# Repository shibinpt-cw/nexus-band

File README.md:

# Nexus Band

A watch that controls the AI assistant on my laptop. I hold the side button and say what I want ("open Notepad, type this and send it to..."), and the assistant on the laptop does it. If an action is risky, the watch asks me first with Approve and Reject buttons.

I'm building it for Hack Club Fallen.

## Why I'm building this

I spend hours at my desk waiting for builds, tests and scripts. When I get up, the laptop sits there until I come back to press Enter or approve something. A normal smartwatch only shows notifications, so it can't help with that.

Nexus Band is a remote for my own assistant, ATS 10, a Python program that runs on the laptop. The watch and the laptop talk over my Wi-Fi. I can walk around the room, tell the laptop what to do, see what it is doing, and approve or reject its actions from my wrist.

## How the watch and the laptop work together

```
  watch (ESP32-S3)                                laptop (ATS 10)
  ---------------                                 ---------------
  hold button + speak  -- 16 kHz audio (WSS) -->  speech -> assistant -> opens apps,
  tap a quick command  -- JSON command (WSS) -->  types, sends messages, runs commands
  Approve / Reject     -- JSON confirm (WSS) -->  continues or cancels the action
  screen + buzz        <-- activity log, confirmation requests --
```

The watch uses the same API as the assistant's phone dashboard:

| Step | Endpoint | What it carries |
|---|---|---|
| Pair | `POST https://<laptop>:8001/login` | one-time key shown on the laptop, returns a token |
| Commands and status | `wss://<laptop>:8001/ws?token=...` | `{"type":"command","text":"..."}`, `{"type":"confirm","decision":"confirm"}`, and the laptop's log and `confirmation_request` messages |
| Voice | `wss://<laptop>:8001/ws/phone-audio?token=...` | raw 16 kHz 16-bit mono audio from the two microphones |

## Hardware

Everything is on one 4-layer PCB, 71 x 40 mm, that sits behind the display. All the parts are on the back, facing the battery, so the front lies flat against the display.

| Block | Part | Notes |
|---|---|---|
| MCU | ESP32-S3-WROOM-1-N16R8 | Wi-Fi, native USB, 16 MB flash, 8 MB PSRAM |
| Display | Newhaven NHD-2.4-240320AF-CSXP-CTP | 2.4" IPS, 240 x 320, ST7789 over SPI, FT5426 capacitive touch |
| Microphones | 2 x ICS-43434 | I2S, 30 mm apart on the right edge |
| Speaker | MAX98357A + 1511 speaker | I2S class-D amplifier |
| Haptics | DRV2605L + LRA motor | wrist buzz when the laptop needs an answer |
| Power | 1000 mAh Li-Po, TP4056 charger, AP2112K 3.3 V | charges at 400 mA from the dock |
| Dock | 4-pin magnetic pogo connector | 5 V charging and USB for flashing |
| Controls | side button (also BOOT), power slide switch | |

### Power and battery life

The slide switch on the bottom edge turns the 3.3 V regulator on and off. With it off, the charger, the battery divider, the amplifier and the haptic driver are still connected, but together they draw about 15 µA, so a charged cell keeps for months. The dock charges the battery with the switch in either position.

I plan to leave the watch switched on and connected all day. The screen turns off after 15 s without use. The side button or a tap wakes it, and so does any message or approval request from the laptop, which also makes the watch buzz.

I haven't measured the runtime yet. My estimate for the 1000 mAh cell is about 10 h with the screen on the whole time and about a day of normal use with the screen sleeping, so it will charge on the dock overnight. If the battery falls below 3.35 V off the dock, the firmware puts the ESP32 into deep sleep to protect the cell.

### Size

The watch body is 85 x 48 mm, or 99 mm across the strap lugs, and 17.5 mm thick. The thickness adds up as bezel 1.0 + display 4.1 + foam 0.5 + PCB 1.6 + parts 3.5 + battery 5.2 + floor 1.4.

### Schematic

PDF: [docs/images/schematic.pdf](docs/images/schematic.pdf)

### PCB

| Back (parts) | Front (display side) |
|---|---|
|  |  |

| 3D, back | 3D, front |
|---|---|
|  |  |

Layer stack: front signal / ground plane / 3.3 V plane / back signal and parts. The strip under the ESP32 antenna has no copper on any layer.

The slot and the notch on the right are for the display's two flex tails. They fold around the board edge and plug into the connectors on the back. That fold reverses the 40-pin connector's numbering: connector pad n is display pin 41 - n. The schematic shows both numbers.

The files in this repo pass KiCad's checks: the [ERC report](docs/erc_report.txt) has 0 violations, and the [DRC report](docs/drc_report.txt) has 0 violations and 0 unconnected pads.

### Pin map

| Function | ESP32-S3 pin |
|---|---|
| Display CS / MOSI / SCK / DC / RST / TE | IO10 / IO11 / IO12 / IO13 / IO14 / IO21 |
| Backlight PWM | IO9 |
| I2C SDA / SCL (touch 0x38, haptics 0x5A) | IO17 / IO18 |
| Touch INT / RST | IO16 / IO15 |
| Microphones SCK / WS / SD | IO5 / IO6 / IO7 |
| Amplifier BCLK / LRCLK / DIN / shutdown | IO40 / IO41 / IO42 / IO39 |
| Battery voltage (1/2 divider) | IO4 |
| Dock detect | IO8 |
| Side button / BOOT | IO0 |
| USB D- / D+ | IO19 / IO20 |

## Case

The case is three parts printed in PETG, and it takes a standard 22 mm quick-release strap.

| Assembled | Exploded |
|---|---|
|  |  |

| Back (strap lugs, screws, speaker grille) | Top edge (charging connector, speaker slots) |
|---|---|
|  |  |

| Part | File | What it does |
|---|---|---|
| Front frame | [`cad/front_frame.step`](cad/front_frame.step) | Bezel with the display window, display pocket, PCB pocket, the two microphone holes (with seats for foam gaskets) and the screw pilots |
| Back shell | [`cad/back_shell.step`](cad/back_shell.step) | Battery, speaker and motor bay with locating ribs, a ledge that clamps the PCB edge, button and power-switch openings on the bottom edge, the charging connector pocket and four speaker slots on the top edge, the speaker grille and four 22 mm strap lugs |
| Button cap | [`cad/button_cap.step`](cad/button_cap.step) | Plunger for the side button; its flange sits inside the back shell |

### Printed parts

| Front frame, outside | Front frame, inside |
|---|---|
|  |  |

| Back shell, inside | Back shell, outside |
|---|---|
|  |  |

| Back shell, top edge | Button cap |
|---|---|
|  |  |

| Part | Size | PETG |
|---|---|---|
| Front frame | 85 x 48 x 7.4 mm | about 13 g |
| Back shell | 99 x 48 x 10.1 mm (with lugs) | about 20 g |
| Button cap | 4.6 x 4.8 x 1.5 mm | under 1 g |

The CAD source is [`cad/nexus_band_case.FCStd`](cad/nexus_band_case.FCStd), made in FreeCAD 1.1. It also holds the PCB, display, battery, speaker and motor as reference parts. The whole assembly is in one file, [`cad/nexus_band_assembly.step`](cad/nexus_band_assembly.step).

### How it fits together

The PCB has no mounting holes, so the case clamps it. The board drops into a 1.6 mm pocket in the front frame, and a 0.8 mm ledge on the back shell presses on its edge. The ledge is cut away where the ESP32 module, the touch connector, the switches and the microphones reach the edge.

The display sits face down in the front frame on 0.5 mm foam tape. The window matches its viewing area, 49.96 x 37.72 mm, which sits 2.5 mm off centre, away from the flex tails.

Four M2 x 12 self-tapping screws go through the ends of the back shell into the front frame. They pass outside the board.

The battery is in the middle and the speaker and motor are on the left. Nothing sits over the antenna strip. The speaker stands on 1 mm pads, which leaves an air gap under it. Sound leaves through the floor grille, a shallow channel to the edge, and four slots in the top edge, so it can still be heard when the floor is against the wrist.

The magnetic dock connector is glued into the pocket on the top edge, next to the dock pads on the PCB. The cable snaps on from the side, and the same connector carries USB for flashing.

Any 22 mm quick-release strap fits. Its spring bars click into the 1.1 mm holes in the lugs without tools.

The power switch lever sits in a slot on the bottom edge. It slides with a fingernail or a toothpick.

### Printing

Print the front frame face down and the back shell floor down, with 0.2 mm layers and no supports.

## Firmware

The firmware is a PlatformIO project in [`firmware/`](firmware). It starts the display, touch, microphones, speaker and haptics, then pairs with the laptop. While I hold the button it streams my voice, and it shows the assistant's messages and confirmation prompts on the screen.

To flash it:

1. Copy the settings block from `firmware/include/config.h` into a new `firmware/include/config_local.h` and fill in the Wi-Fi name, password, laptop address and the one-time key the laptop shows.
2. Put the watch on the dock, hold the side button while connecting it the first time, then `pio run -t upload`.

The firmware compiles with `pio run` and takes about 1 MB of the 16 MB flash. It has not run on hardware yet, because the board is not built.

## Building one

Nobody has built this watch yet, including me, so treat these steps as the plan. I will correct them after my own build.

### 1. Order the board

Upload three files from [`pcb/`](pcb) to JLCPCB: `gerbers.zip` for the board, `jlcpcb_bom.csv` for the parts and `jlcpcb_cpl.csv` for the part positions. Choose 4 layers, 1.6 mm, HASL, and assembly on the bottom side. Check the part rotations in JLCPCB's preview before paying, because their rotation convention sometimes differs from KiCad's.

The factory fits every part on the board except the 6-pin touch connector, J2. That one comes from DigiKey and has a 1.0 mm pitch, so a normal soldering iron can do it.

### 2. Order the rest

[`bom.csv`](bom.csv) lists everything else with a link: the display, touch connector, speaker, vibration motor and magnetic connector from DigiKey, the battery, a 22 mm strap, four M2 x 12 screws and 0.5 mm foam tape. The battery must have its own protection board, because the PCB does not have one.

### 3. Print the case

Print `front_frame.step`, `back_shell.step` and `button_cap.step` from [`cad/`](cad) in PETG with 0.2 mm layers and no supports. The front frame prints face down and the back shell prints floor down. Measure the magnetic connector first. The pocket for it is 13.5 x 5 mm, and if your connector is a different size you can change the pocket in `nexus_band_case.FCStd`.

### 4. Solder the wires

Solder the touch connector J2 to the board. Then solder wires to the labelled pads on the back: the battery to B+ and B-, the speaker to S+ and S-, the motor to M+ and M-, and the magnetic connector to the four dock pads marked 5V, D-, D+ and GND. Fit the other half of the magnetic connector to a cut USB cable with the same four wires. Leave the power switch off while you solder the battery.

### 5. Test before closing the case

Plug in the dock cable. The red LED means charging and the green LED means full. Switch the watch on and flash the firmware (see [Firmware](#firmware)). Check the screen, touch, both microphones, the speaker and the buzz before the board goes into the case.

### 6. Assemble

1. Stick 0.5 mm foam tape on the front of the PCB, with small rings around the two microphone holes.
2. Lay the display face down in the front frame. Fold its two flex tails through the slot and the notch in the PCB, and lock them into J1 and J2 on the back.
3. Lower the PCB into its pocket in the front frame.
4. Put the speaker on its four pads in the back shell with the sound side down, press the motor into its ring, glue the magnetic connector into its pocket, and lay the battery in the middle.
5. Drop the button cap into its slot on the bottom edge.
6. Close the back shell over the front frame and fit the four screws.
7. Click the strap's spring bars into the lugs.

## Repository

```
nexus-band/
├── README.md
├── bom.csv                  parts list with links
├── pcb/                     KiCad 10 project
│   ├── nexus_band.kicad_pro / .kicad_sch / .kicad_pcb / .kicad_prl
│   ├── nexus_band.pretty/   footprints for the wire pads
│   ├── gerbers.zip          fabrication files (gerbers + drill)
│   ├── jlcpcb_bom.csv       parts list in JLCPCB's format, with LCSC numbers
│   ├── jlcpcb_cpl.csv       part positions in JLCPCB's format
│   └── nexus_band-pos.csv   pick-and-place positions as KiCad exports them
├── cad/                     case parts (STEP), FreeCAD source, PCB and assembly models
├── firmware/                ESP32-S3 firmware (PlatformIO)
└── docs/                    schematic PDF, renders, ERC / DRC reports
```

## Bill of materials

The first working watch costs about $252. That pays for a 5-board PCB order with two boards assembled, which is the factory minimum. It also covers the display, battery, speaker, motor, dock connector, strap and case screws, a 1 kg spool of PETG for the case, a soldering iron, shipping and import duty. The JLCPCB fees, shipping and duty lines are estimates until I have real quotes, and so are the strap, screws and foam tape, which are generic parts that any shop sells. The full list with links is in [`bom.csv`](bom.csv).

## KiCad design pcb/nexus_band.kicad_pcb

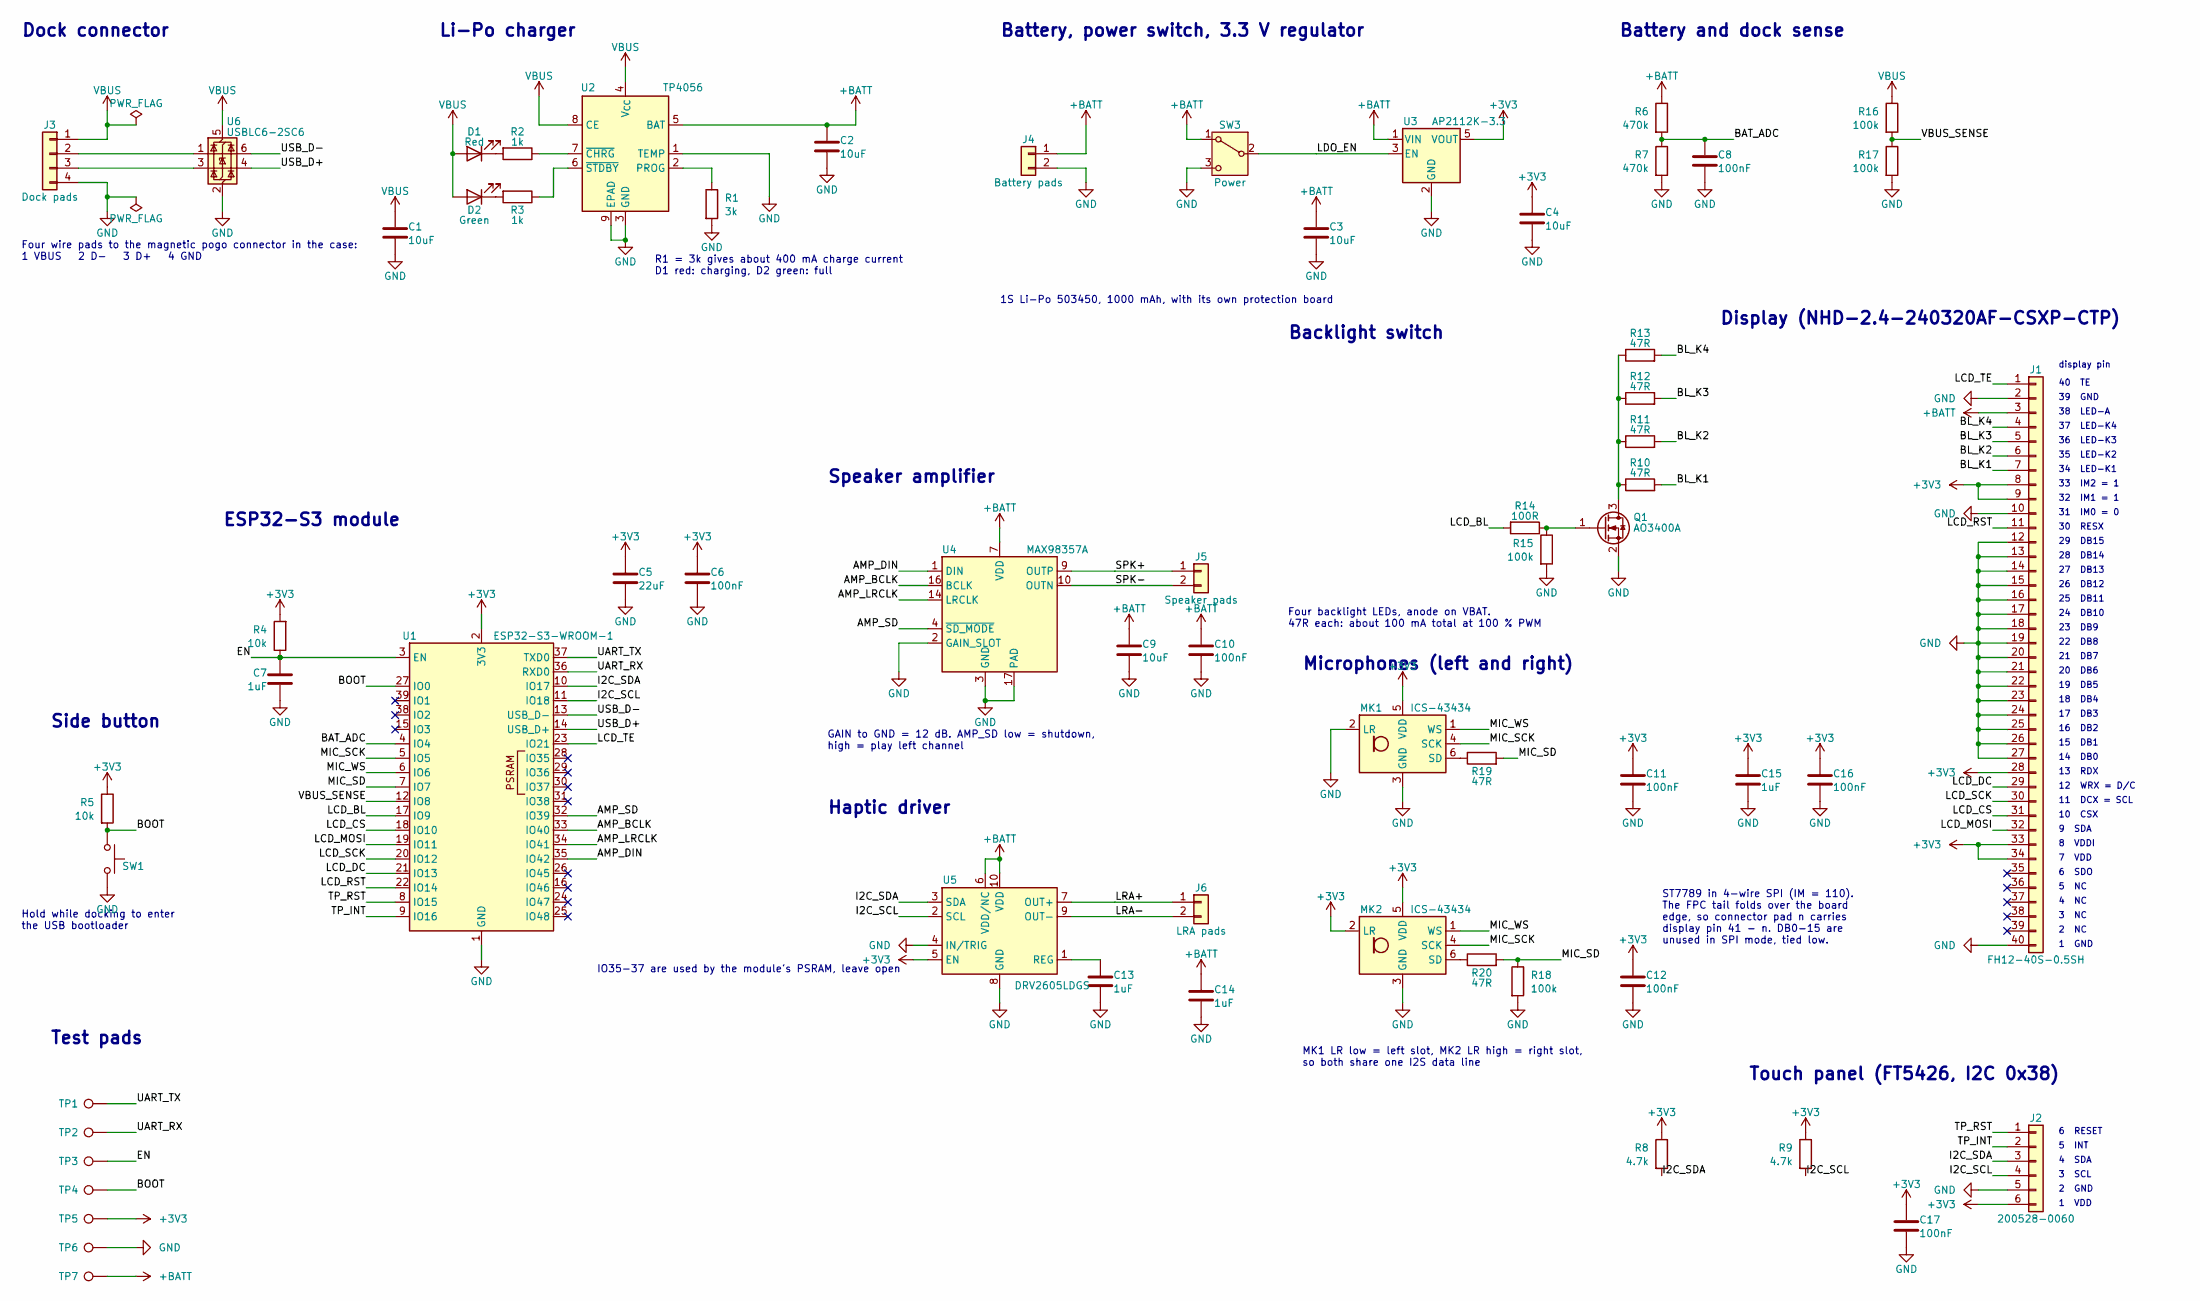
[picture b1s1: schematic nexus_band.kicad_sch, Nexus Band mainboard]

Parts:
C1, C2, C3, C4, C9: 10uF; C_0603_1608Metric
C5: 22uF; C_0805_2012Metric
C6, C8, C10, C11, C12, C16, C17: 100nF; C_0603_1608Metric
C7, C13, C14, C15: 1uF; C_0603_1608Metric
D1: Red; LED_0603_1608Metric
D2: Green; LED_0603_1608Metric
J1: FH12-40S-0.5SH; Hirose_FH12-40S-0.5SH_1x40-1MP_P0.50mm_Horizontal; MPN FH12-40S-0.5SH(55)
J2: 200528-0060; Molex_200528-0060_1x06-1MP_P1.00mm_Horizontal; MPN 2005280060
J3: Dock pads; WirePads_1x04_P2.54mm
J4: Battery pads; WirePads_1x02_P2.54mm
J5: Speaker pads; WirePads_1x02_P2.54mm
J6: LRA pads; WirePads_1x02_P2.54mm
MK1, MK2: ICS-43434; InvenSense_ICS-43434-6_3.5x2.65mm; MPN ICS-43434
Q1: AO3400A; SOT-23; MPN AO3400A
R1: 3k; R_0603_1608Metric
R2, R3: 1k; R_0603_1608Metric
R4, R5: 10k; R_0603_1608Metric
R6, R7: 470k; R_0603_1608Metric
R8, R9: 4.7k; R_0603_1608Metric
R10, R11, R12, R13, R19, R20: 47R; R_0603_1608Metric
R14: 100R; R_0603_1608Metric
R15, R16, R17, R18: 100k; R_0603_1608Metric
SW1: B3U-3000P; SW_SPST_B3U-3000P; MPN B3U-3000P
SW3: Power; SW_SPDT_PCM12; MPN PCM12SMTR
TP1: UART_TX; TestPoint_Pad_D1.5mm
TP2: UART_RX; TestPoint_Pad_D1.5mm
TP3: EN; TestPoint_Pad_D1.5mm
TP4: BOOT; TestPoint_Pad_D1.5mm
TP5: +3V3; TestPoint_Pad_D1.5mm
TP6: GND; TestPoint_Pad_D1.5mm
TP7: +BATT; TestPoint_Pad_D1.5mm
U1: ESP32-S3-WROOM-1; MPN ESP32-S3-WROOM-1-N16R8
U2: TP4056; SOIC-8-1EP_3.9x4.9mm_P1.27mm_EP2.41x3.3mm; MPN TP4056
U3: AP2112K-3.3; SOT-23-5; MPN AP2112K-3.3TRG1
U4: MAX98357A; TQFN-16-1EP_3x3mm_P0.5mm_EP1.23x1.23mm; MPN MAX98357AETE+T
U5: DRV2605LDGS; TSSOP-10_3x3mm_P0.5mm; MPN DRV2605LDGSR
U6: USBLC6-2SC6; SOT-23-6; MPN USBLC6-2SC6

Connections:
+3V3: C4.1, C5.1, C6.1, C11.1, C12.1, C15.1, C16.1, C17.1, J1.8, J1.9, J1.28, J1.33, J1.34, J2.6, MK1.5 (VDD), MK2.2 (LR), MK2.5 (VDD), R4.2, R5.1, R8.1, R9.1, TP5.1, U1.2 (3V3), U3.5 (VOUT), U5.5 (EN)
+BATT: C2.1, C3.1, C9.1, C10.1, C14.1, J1.3, J4.1, R6.1, SW3.1 (A), TP7.1, U2.5 (BAT), U3.1 (VIN), U4.7 (VDD), U4.8 (VDD), U5.6 (VDD/NC), U5.10 (VDD)
/AMP_BCLK: U1.33 (IO40), U4.16 (BCLK)
/AMP_DIN: U1.35 (IO42), U4.1 (DIN)
/AMP_LRCLK: U1.34 (IO41), U4.14 (LRCLK)
/AMP_SD: U1.32 (IO39), U4.4 (~SD_MODE)
/BAT_ADC: C8.1, R6.2, R7.1, U1.4 (IO4)
/BL_K1: J1.7, R10.2
/BL_K2: J1.6, R11.2
/BL_K3: J1.5, R12.2
/BL_K4: J1.4, R13.2
/BOOT: R5.2, SW1.1, TP4.1, U1.27 (IO0)
/EN: C7.1, R4.1, TP3.1, U1.3 (EN)
/I2C_SCL: J2.4, R9.2, U1.11 (IO18), U5.2 (SCL)
/I2C_SDA: J2.3, R8.2, U1.10 (IO17), U5.3 (SDA)
/LCD_BL: R14.2, U1.17 (IO9)
/LCD_CS: J1.31, U1.18 (IO10)
/LCD_DC: J1.29, U1.21 (IO13)
/LCD_MOSI: J1.32, U1.19 (IO11)
/LCD_RST: J1.11, U1.22 (IO14)
/LCD_SCK: J1.30, U1.20 (IO12)
/LCD_TE: J1.1, U1.23 (IO21)
/LDO_EN: SW3.2 (B), U3.3 (EN)
/LRA+: J6.1, U5.7 (OUT+)
/LRA-: J6.2, U5.9 (OUT-)
/MIC_SCK: MK1.4 (SCK), MK2.4 (SCK), U1.5 (IO5)
/MIC_SD: R18.1, R19.2, R20.2, U1.7 (IO7)
/MIC_WS: MK1.1 (WS), MK2.1 (WS), U1.6 (IO6)
/SPK+: J5.1, U4.9 (OUTP)
/SPK-: J5.2, U4.10 (OUTN)
/TP_INT: J2.2, U1.9 (IO16)
/TP_RST: J2.1, U1.8 (IO15)
/UART_RX: TP2.1, U1.36 (RXD0)
/UART_TX: TP1.1, U1.37 (TXD0)
/USB_D+: U1.14 (USB_D+), U6.4 (I/O2)
/USB_D-: U1.13 (USB_D-), U6.6 (I/O1)
/VBUS_SENSE: R16.2, R17.1, U1.12 (IO8)
GND: C1.2, C2.2, C3.2, C4.2, C5.2, C6.2, C7.2, C8.2, C9.2, C10.2, C11.2, C12.2, C13.2, C14.2, C15.2, C16.2, C17.2, J1.2, J1.10, J1.12, J1.13, J1.14, J1.15, J1.16, J1.17, J1.18, J1.19, J1.20, J1.21, J1.22, J1.23, J1.24, J1.25, J1.26, J1.27, J1.40, J2.5, J3.4, J4.2, MK1.2 (LR), MK1.3 (GND), MK2.3 (GND), Q1.2 (S), R1.2, R7.2, R15.2, R17.2, R18.2, SW1.2, SW3.3 (C), TP6.1, U1.1 (GND), U1.40 (GND), U1.41 (GND), U2.1 (TEMP), U2.3 (GND), U2.9 (EPAD), U3.2 (GND), U4.2 (GAIN_SLOT), U4.3 (GND), U4.11 (GND), U4.15 (GND), U4.17 (PAD), U5.4 (IN/TRIG), U5.8 (GND), U6.2 (GND)
unnamed: D1.1 (K), R2.2
unnamed: D2.1 (K), R3.2
unnamed: J3.2, U6.1 (I/O1)
unnamed: J3.3, U6.3 (I/O2)
unnamed: MK1.6 (SD), R19.1
unnamed: MK2.6 (SD), R20.1
unnamed: Q1.3 (D), R10.1, R11.1, R12.1, R13.1
unnamed: Q1.1 (G), R14.1, R15.1
unnamed: R1.1, U2.2 (PROG)
unnamed: R2.1, U2.7 (~CHRG)
unnamed: R3.1, U2.6 (~STDBY)
unnamed: C13.1, U5.1 (REG)
VBUS: C1.1, D1.2 (A), D2.2 (A), J3.1, R16.1, U2.4 (V_{CC}), U2.8 (CE), U6.5 (VBUS)

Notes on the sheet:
Dock connector
Four wire pads to the magnetic pogo connector in the case: 1 VBUS 2 D- 3 D+ 4 GND
Li-Po charger
R1 = 3k gives about 400 mA charge current D1 red: charging, D2 green: full
Battery, power switch, 3.3 V regulator
1S Li-Po 503450, 1000 mAh, with its own protection board
Battery and dock sense
ESP32-S3 module
IO35-37 are used by the module's PSRAM, leave open
Side button
Hold while docking to enter the USB bootloader
Test pads
Speaker amplifier
GAIN to GND = 12 dB. AMP_SD low = shutdown, high = play left channel
Haptic driver
Microphones (left and right)
MK1 LR low = left slot, MK2 LR high = right slot, so both share one I2S data line
Backlight switch
Four backlight LEDs, anode on VBAT. 47R each: about 100 mA total at 100 % PWM
Display (NHD-2.4-240320AF-CSXP-CTP)
40 TE
39 GND
38 LED-A
37 LED-K4
36 LED-K3
35 LED-K2
34 LED-K1
33 IM2 = 1
32 IM1 = 1
31 IM0 = 0
30 RESX
29 DB15
28 DB14
27 DB13
26 DB12
25 DB11
24 DB10
23 DB9
22 DB8
21 DB7

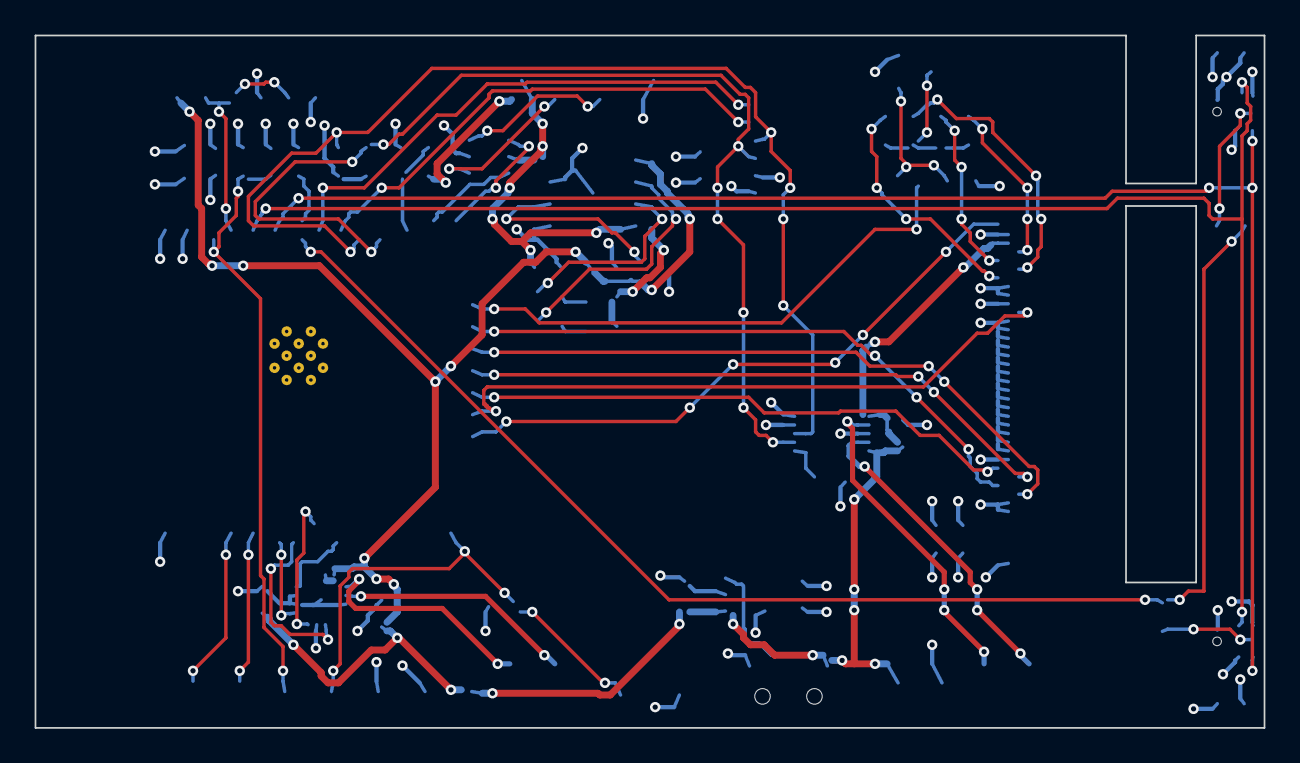
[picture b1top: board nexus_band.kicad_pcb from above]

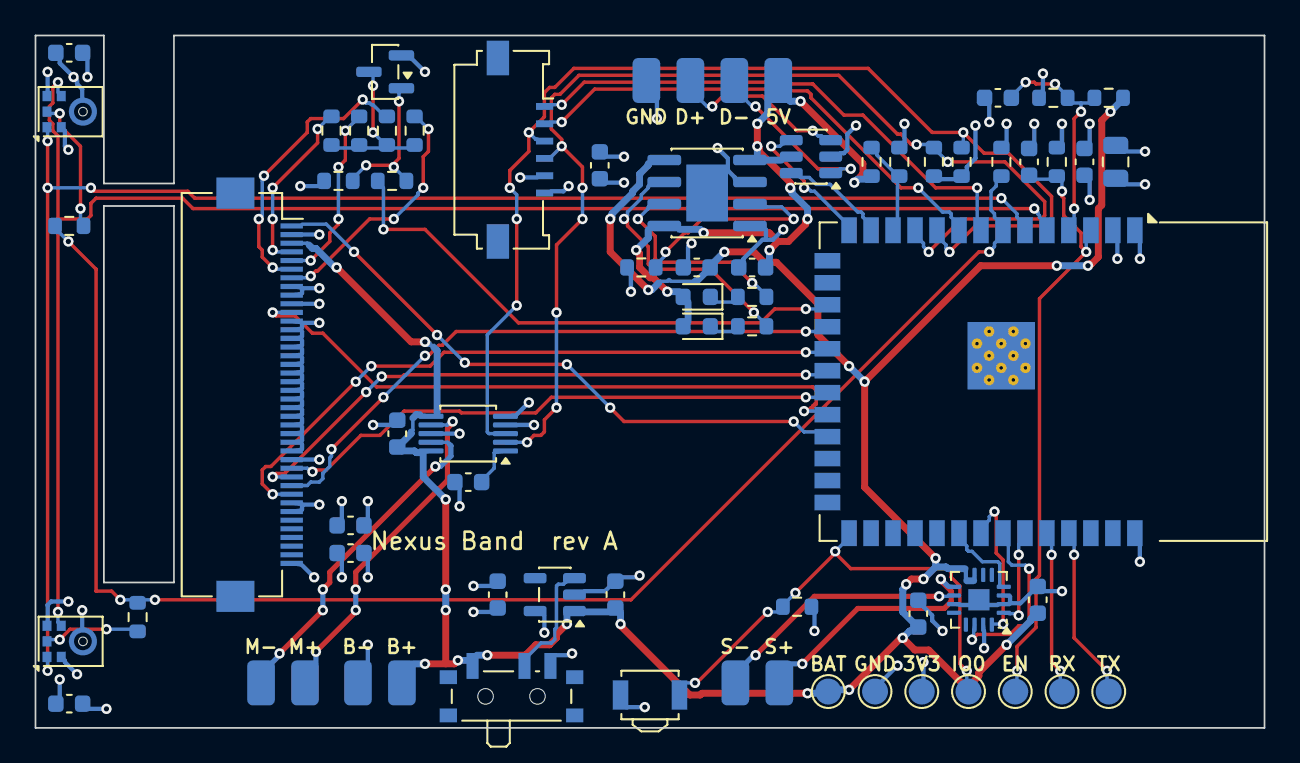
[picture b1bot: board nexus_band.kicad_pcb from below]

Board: 4 copper layers, 71.0 x 40.0 mm, 63 parts (63 on the bottom side), 51 nets.

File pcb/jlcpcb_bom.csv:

Comment,Designator,Footprint,LCSC Part #
10uF,"C1,C2,C3,C4,C9",C_0603_1608Metric,C19702
22uF,C5,C_0805_2012Metric,C45783
100nF,"C6,C8,C10,C11,C12,C16,C17",C_0603_1608Metric,C14663
1uF,"C7,C13,C14,C15",C_0603_1608Metric,C15849
Red,D1,LED_0603_1608Metric,C2286
Green,D2,LED_0603_1608Metric,C12624
FH12-40S-0.5SH,J1,Hirose_FH12-40S-0.5SH_1x40-1MP_P0.50mm_Horizontal,C202114
ICS-43434,"MK1,MK2",InvenSense_ICS-43434-6_3.5x2.65mm,C5656610
AO3400A,Q1,SOT-23,C20917
3k,R1,R_0603_1608Metric,C4211
1k,"R2,R3",R_0603_1608Metric,C21190
10k,"R4,R5",R_0603_1608Metric,C25804
470k,"R6,R7",R_0603_1608Metric,C23178
4.7k,"R8,R9",R_0603_1608Metric,C23162
47R,"R10,R11,R12,R13,R19,R20",R_0603_1608Metric,C23182
100R,R14,R_0603_1608Metric,C22775
100k,"R15,R16,R17,R18",R_0603_1608Metric,C25803
B3U-3000P,SW1,SW_SPST_B3U-3000P,C963349
Power,SW3,SW_SPDT_PCM12,C221841
ESP32-S3-WROOM-1,U1,ESP32-S3-WROOM-1,C2913202
TP4056,U2,SOIC-8-1EP_3.9x4.9mm_P1.27mm_EP2.41x3.3mm,C16581
AP2112K-3.3,U3,SOT-23-5,C51118
MAX98357A,U4,TQFN-16-1EP_3x3mm_P0.5mm_EP1.23x1.23mm,C910544
DRV2605LDGS,U5,TSSOP-10_3x3mm_P0.5mm,C527464
USBLC6-2SC6,U6,SOT-23-6,C7519

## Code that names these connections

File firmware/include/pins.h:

// Pin map of the Nexus Band mainboard, rev A.
// Keep this file in step with pcb/nexus_band.kicad_sch.
#pragma once

// Display: ST7789 over 4-wire SPI (Newhaven NHD-2.4-240320AF-CSXP-CTP)
#define PIN_LCD_CS    10
#define PIN_LCD_MOSI  11
#define PIN_LCD_SCK   12
#define PIN_LCD_DC    13
#define PIN_LCD_RST   14
#define PIN_LCD_TE    21   // tearing-effect output from the panel (optional)
#define PIN_LCD_BL     9   // PWM, high = backlight on (N-MOSFET low side)

// Touch panel (FT5426, address 0x38) and haptic driver (DRV2605L, 0x5A) share I2C
#define PIN_I2C_SDA   17
#define PIN_I2C_SCL   18
#define PIN_TP_INT    16
#define PIN_TP_RST    15

// Two ICS-43434 microphones on one I2S bus (MK1 = left slot, MK2 = right slot)
#define PIN_MIC_SCK    5
#define PIN_MIC_WS     6
#define PIN_MIC_SD     7

// MAX98357A speaker amplifier
#define PIN_AMP_BCLK  40
#define PIN_AMP_LRCLK 41
#define PIN_AMP_DIN   42
#define PIN_AMP_SD    39   // low = shutdown, high = on (left channel)

// Power
#define PIN_BAT_ADC    4   // VBAT through 470k / 470k  ->  VBAT = 2 x reading
#define PIN_VBUS_SENSE 8   // dock 5 V through 100k / 100k, about 2.5 V when docked

// Side button, also the BOOT strap (active low, 10k pull-up on the board)
#define PIN_BUTTON     0
